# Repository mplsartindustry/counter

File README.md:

# counter

Eurorack module that counts triggers

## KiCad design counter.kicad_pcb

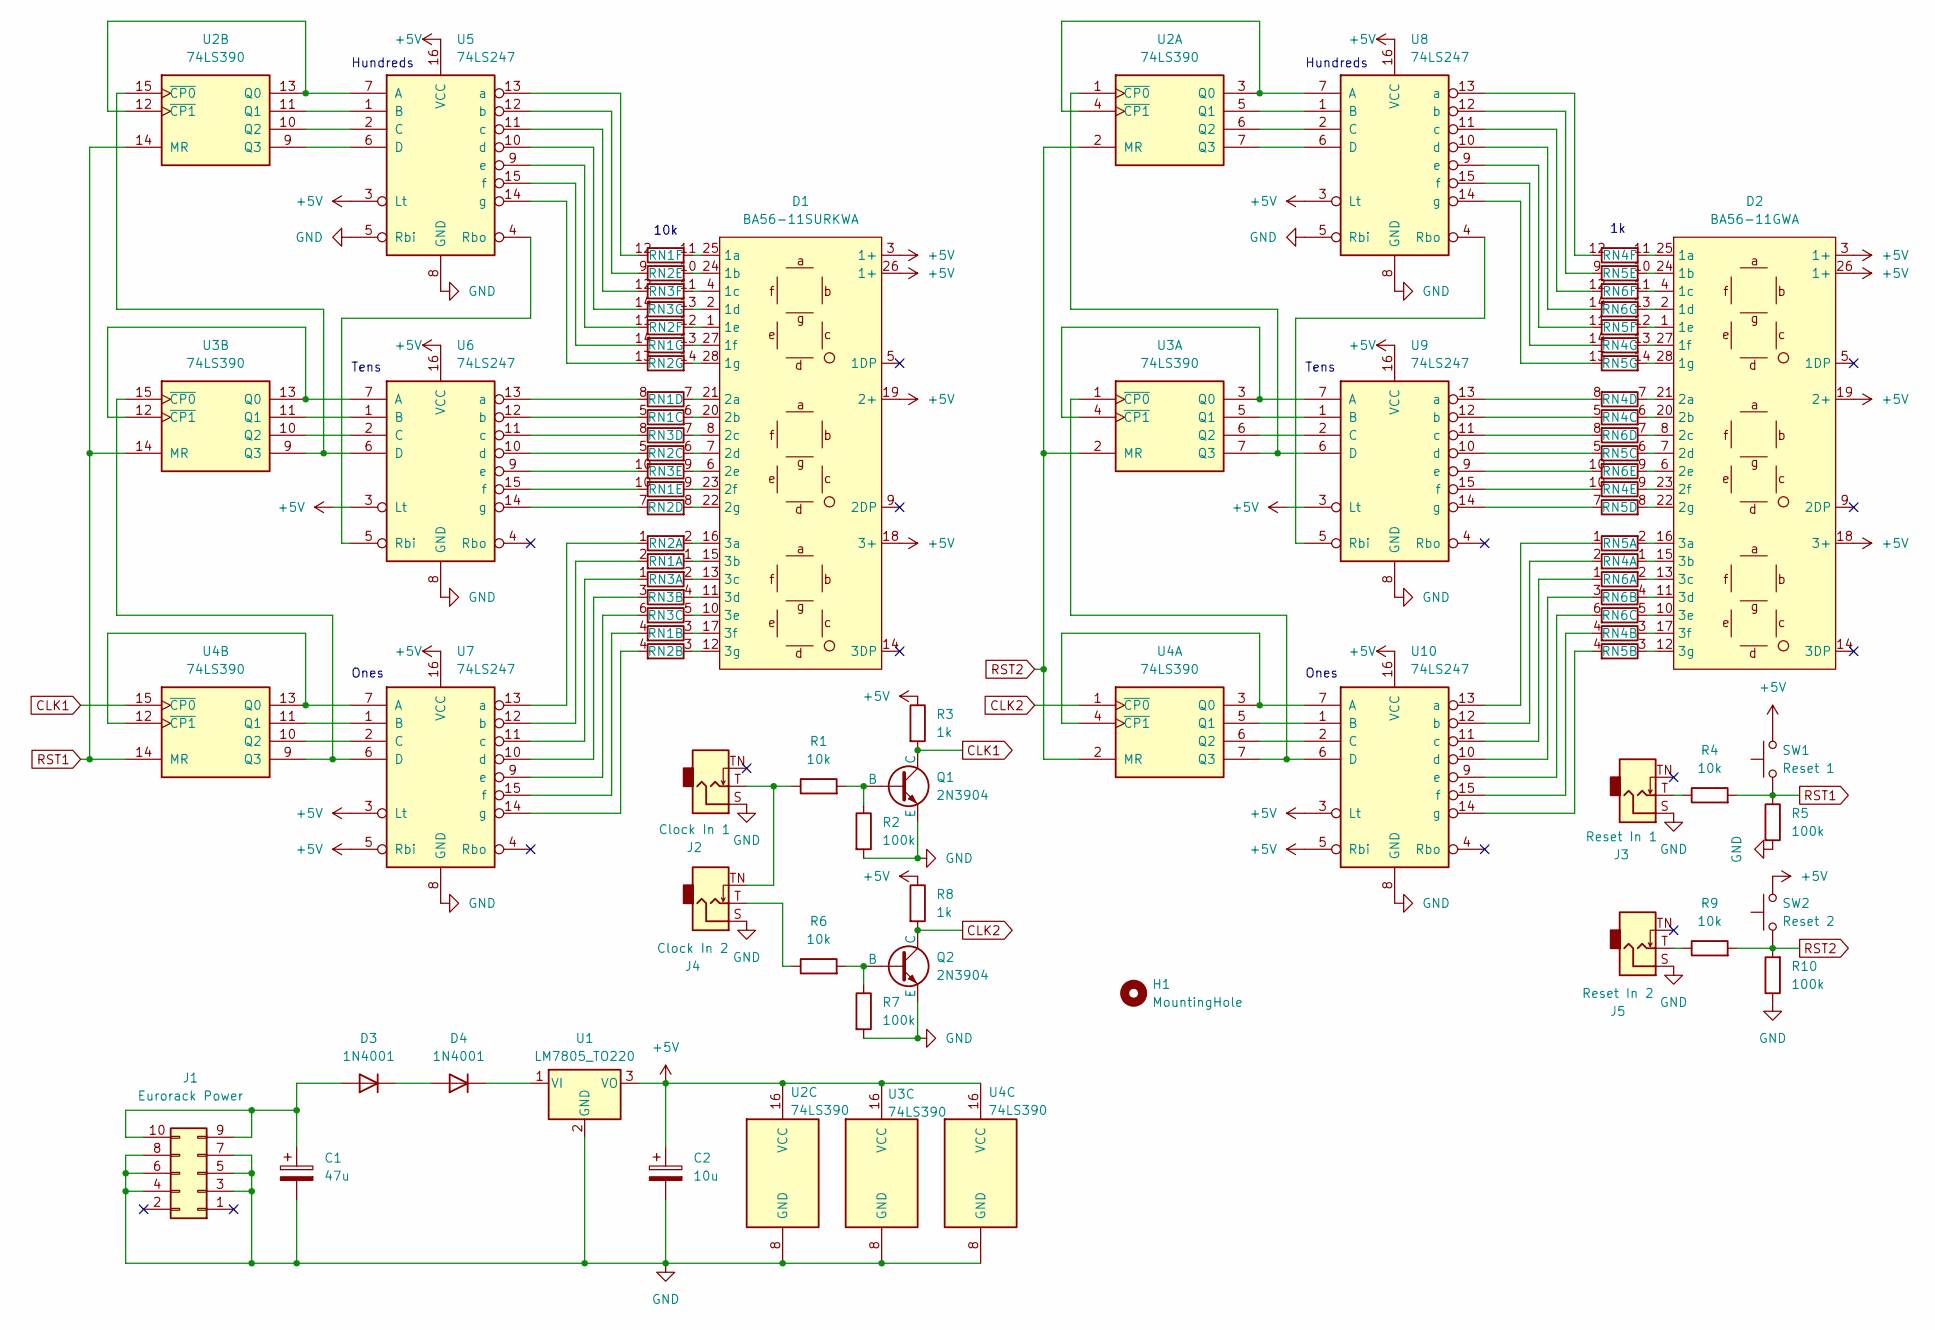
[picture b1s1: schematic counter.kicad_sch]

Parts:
C1: 47u; CP_Radial_D5.0mm_P2.00mm
C2: 10u; CP_Radial_D5.0mm_P2.00mm
D1: BA56-11SURKWA; BA56-11SURKWA_Red_2xSIP
D2: BA56-11GWA; BA56-11GWA_Green_2xSIP
D3, D4: 1N4001; D_DO-41_SOD81_P10.16mm_Horizontal
H1: MountingHole; MountingHole_4.3mm_M4
J1: Eurorack Power; IDC-Header_2x05_P2.54mm_Vertical
J2: Clock In 1; Jack_3.5mm_QingPu_WQP-PJ301BM_Vertical
J3: Reset In 1; Jack_3.5mm_QingPu_WQP-PJ301BM_Vertical
J4: Clock In 2; Jack_3.5mm_QingPu_WQP-PJ301BM_Vertical
J5: Reset In 2; Jack_3.5mm_QingPu_WQP-PJ301BM_Vertical
Q1, Q2: 2N3904; TO-92L_Inline
R1, R4, R6, R9: 10k; R_Axial_DIN0207_L6.3mm_D2.5mm_P7.62mm_Horizontal
R2, R5, R7, R10: 100k; R_Axial_DIN0207_L6.3mm_D2.5mm_P7.62mm_Horizontal
R3, R8: 1k; R_Axial_DIN0207_L6.3mm_D2.5mm_P7.62mm_Horizontal
RN1, RN2, RN3, RN4, RN5, RN6: R_Pack07_SIP_Split; R_Array_SIP14
SW1: Reset 1; SW_CK_D6R40_Red
SW2: Reset 2; SW_CK_D6R50_Green
U1: LM7805_TO220; TO-220-3_Vertical
U2, U3, U4: 74LS390; DIP-16_W7.62mm_Socket_WithChip
U5, U6, U7, U8, U9, U10: 74LS247; DIP-16_W7.62mm_Socket_WithChip

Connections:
+5V: C2.1, D1.3 (1+), D1.18 (3+), D1.19 (2+), D1.26 (1+), D2.3 (1+), D2.18 (3+), D2.19 (2+), D2.26 (1+), R3.1, R8.1, SW1.2, SW2.2, U1.3 (VO), U2.16 (VCC), U3.16 (VCC), U4.16 (VCC), U5.3 (Lt), U5.16 (VCC), U6.3 (Lt), U6.16 (VCC), U7.3 (Lt), U7.5 (Rbi), U7.16 (VCC), U8.3 (Lt), U8.16 (VCC), U9.3 (Lt), U9.16 (VCC), U10.3 (Lt), U10.5 (Rbi), U10.16 (VCC)
CLK1: Q1.1 (C), R3.2, U4.15 (~CP0)
CLK2: Q2.1 (C), R8.2, U4.1 (~CP0)
GND: C1.2, C2.2, J1.3, J1.4, J1.5, J1.6, J1.7, J1.8, J2.S, J3.S, J4.S, J5.S, Q1.3 (E), Q2.3 (E), R2.2, R5.2, R7.2, R10.1, U1.2 (GND), U2.8 (GND), U3.8 (GND), U4.8 (GND), U5.5 (Rbi), U5.8 (GND), U6.8 (GND), U7.8 (GND), U8.5 (Rbi), U8.8 (GND), U9.8 (GND), U10.8 (GND)
unnamed: D1.25 (1a), RN1.11 (R6.1)
unnamed: D1.24 (1b), RN2.10 (R5.2)
unnamed: D1.4 (1c), RN3.11 (R6.1)
unnamed: D1.2 (1d), RN3.13 (R7.1)
unnamed: D1.1 (1e), RN2.12 (R6.2)
unnamed: D1.27 (1f), RN1.13 (R7.1)
unnamed: D1.28 (1g), RN2.14 (R7.2)
unnamed: D1.21 (2a), RN1.7 (R4.1)
unnamed: D1.20 (2b), RN1.6 (R3.2)
unnamed: D1.8 (2c), RN3.7 (R4.1)
unnamed: D1.7 (2d), RN2.6 (R3.2)
unnamed: D1.6 (2e), RN3.9 (R5.1)
unnamed: D1.23 (2f), RN1.9 (R5.1)
unnamed: D1.22 (2g), RN2.8 (R4.2)
unnamed: D1.16 (3a), RN2.2 (R1.2)
unnamed: D1.15 (3b), RN1.1 (R1.1)
unnamed: D1.13 (3c), RN3.2 (R1.2)
unnamed: D1.11 (3d), RN3.4 (R2.2)
unnamed: D1.10 (3e), RN3.5 (R3.1)
unnamed: D1.17 (3f), RN1.3 (R2.1)
unnamed: D1.12 (3g), RN2.3 (R2.1)
unnamed: D2.25 (1a), RN4.11 (R6.1)
unnamed: D2.24 (1b), RN5.10 (R5.2)
unnamed: D2.4 (1c), RN6.11 (R6.1)
unnamed: D2.2 (1d), RN6.13 (R7.1)
unnamed: D2.1 (1e), RN5.12 (R6.2)
unnamed: D2.27 (1f), RN4.13 (R7.1)
unnamed: D2.28 (1g), RN5.14 (R7.2)
unnamed: D2.21 (2a), RN4.7 (R4.1)
unnamed: D2.20 (2b), RN4.6 (R3.2)
unnamed: D2.8 (2c), RN6.7 (R4.1)
unnamed: D2.7 (2d), RN5.6 (R3.2)
unnamed: D2.6 (2e), RN6.9 (R5.1)
unnamed: D2.23 (2f), RN4.9 (R5.1)
unnamed: D2.22 (2g), RN5.8 (R4.2)
unnamed: D2.16 (3a), RN5.2 (R1.2)
unnamed: D2.15 (3b), RN4.1 (R1.1)
unnamed: D2.13 (3c), RN6.2 (R1.2)
unnamed: D2.11 (3d), RN6.4 (R2.2)
unnamed: D2.10 (3e), RN6.5 (R3.1)
unnamed: D2.17 (3f), RN4.3 (R2.1)
unnamed: D2.12 (3g), RN5.3 (R2.1)
unnamed: C1.1, D3.2 (A), J1.9, J1.10
unnamed: D3.1 (K), D4.2 (A)
unnamed: D4.1 (K), U1.1 (VI)
unnamed: J2.T, J4.TN, R1.1
unnamed: J3.T, R4.1
unnamed: J4.T, R6.1
unnamed: J5.T, R9.1
unnamed: Q1.2 (B), R1.2, R2.1
unnamed: Q2.2 (B), R6.2, R7.1
unnamed: RN1.2 (R1.2), U7.12 (b)
unnamed: RN1.4 (R2.2), U7.15 (f)
unnamed: RN1.5 (R3.1), U6.12 (b)
unnamed: RN1.8 (R4.2), U6.13 (a)
unnamed: RN1.10 (R5.2), U6.15 (f)
unnamed: RN1.12 (R6.2), U5.13 (a)
unnamed: RN1.14 (R7.2), U5.15 (f)
unnamed: RN2.1 (R1.1), U7.13 (a)
unnamed: RN2.4 (R2.2), U7.14 (g)
unnamed: RN2.5 (R3.1), U6.10 (d)
unnamed: RN2.7 (R4.1), U6.14 (g)
unnamed: RN2.9 (R5.1), U5.12 (b)
unnamed: RN2.11 (R6.1), U5.9 (e)
unnamed: RN2.13 (R7.1), U5.14 (g)
unnamed: RN3.1 (R1.1), U7.11 (c)
unnamed: RN3.3 (R2.1), U7.10 (d)
unnamed: RN3.6 (R3.2), U7.9 (e)
unnamed: RN3.8 (R4.2), U6.11 (c)
unnamed: RN3.10 (R5.2), U6.9 (e)
unnamed: RN3.12 (R6.2), U5.11 (c)
unnamed: RN3.14 (R7.2), U5.10 (d)
unnamed: RN4.2 (R1.2), U10.12 (b)
unnamed: RN4.4 (R2.2), U10.15 (f)
unnamed: RN4.5 (R3.1), U9.12 (b)
unnamed: RN4.8 (R4.2), U9.13 (a)
unnamed: RN4.10 (R5.2), U9.15 (f)
unnamed: RN4.12 (R6.2), U8.13 (a)
unnamed: RN4.14 (R7.2), U8.15 (f)
unnamed: RN5.1 (R1.1), U10.13 (a)
unnamed: RN5.4 (R2.2), U10.14 (g)
unnamed: RN5.5 (R3.1), U9.10 (d)
unnamed: RN5.7 (R4.1), U9.14 (g)
unnamed: RN5.9 (R5.1), U8.12 (b)
unnamed: RN5.11 (R6.1), U8.9 (e)
unnamed: RN5.13 (R7.1), U8.14 (g)
unnamed: RN6.1 (R1.1), U10.11 (c)
unnamed: RN6.3 (R2.1), U10.10 (d)
unnamed: RN6.6 (R3.2), U10.9 (e)
unnamed: RN6.8 (R4.2), U9.11 (c)
unnamed: RN6.10 (R5.2), U9.9 (e)
unnamed: RN6.12 (R6.2), U8.11 (c)
unnamed: RN6.14 (R7.2), U8.10 (d)
unnamed: U2.3 (Q0), U2.4 (~CP1), U8.7 (A)
unnamed: U2.5 (Q1), U8.1 (B)
unnamed: U2.6 (Q2), U8.2 (C)
unnamed: U2.7 (Q3), U8.6 (D)
unnamed: U2.1 (~CP0), U3.7 (Q3), U9.6 (D)
unnamed: U2.12 (~CP1), U2.13 (Q0), U5.7 (A)
unnamed: U2.11 (Q1), U5.1 (B)
unnamed: U2.10 (Q2), U5.2 (C)
unnamed: U2.9 (Q3), U5.6 (D)
unnamed: U2.15 (~CP0), U3.9 (Q3), U6.6 (D)
unnamed: U3.3 (Q0), U3.4 (~CP1), U9.7 (A)
unnamed: U3.5 (Q1), U9.1 (B)
unnamed: U3.6 (Q2), U9.2 (C)
unnamed: U3.12 (~CP1), U3.13 (Q0), U6.7 (A)
unnamed: U3.11 (Q1), U6.1 (B)
unnamed: U3.10 (Q2), U6.2 (C)
unnamed: U3.15 (~CP0), U4.9 (Q3), U7.6 (D)
unnamed: U4.12 (~CP1), U4.13 (Q0), U7.7 (A)
unnamed: U4.11 (Q1), U7.1 (B)
unnamed: U4.10 (Q2), U7.2 (C)
unnamed: U5.4 (Rbo), U6.5 (Rbi)
unnamed: U8.4 (Rbo), U9.5 (Rbi)
unnamed: U4.3 (Q0), U4.4 (~CP1), U10.7 (A)
unnamed: U4.5 (Q1), U10.1 (B)
unnamed: U4.6 (Q2), U10.2 (C)
unnamed: U3.1 (~CP0), U4.7 (Q3), U10.6 (D)
RST1: R4.2, R5.1, SW1.1, U2.14 (MR), U3.14 (MR), U4.14 (MR)
RST2: R9.2, R10.2, SW2.1, U2.2 (MR), U3.2 (MR), U4.2 (MR)

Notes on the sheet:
Ones
Tens
Hundreds
10k

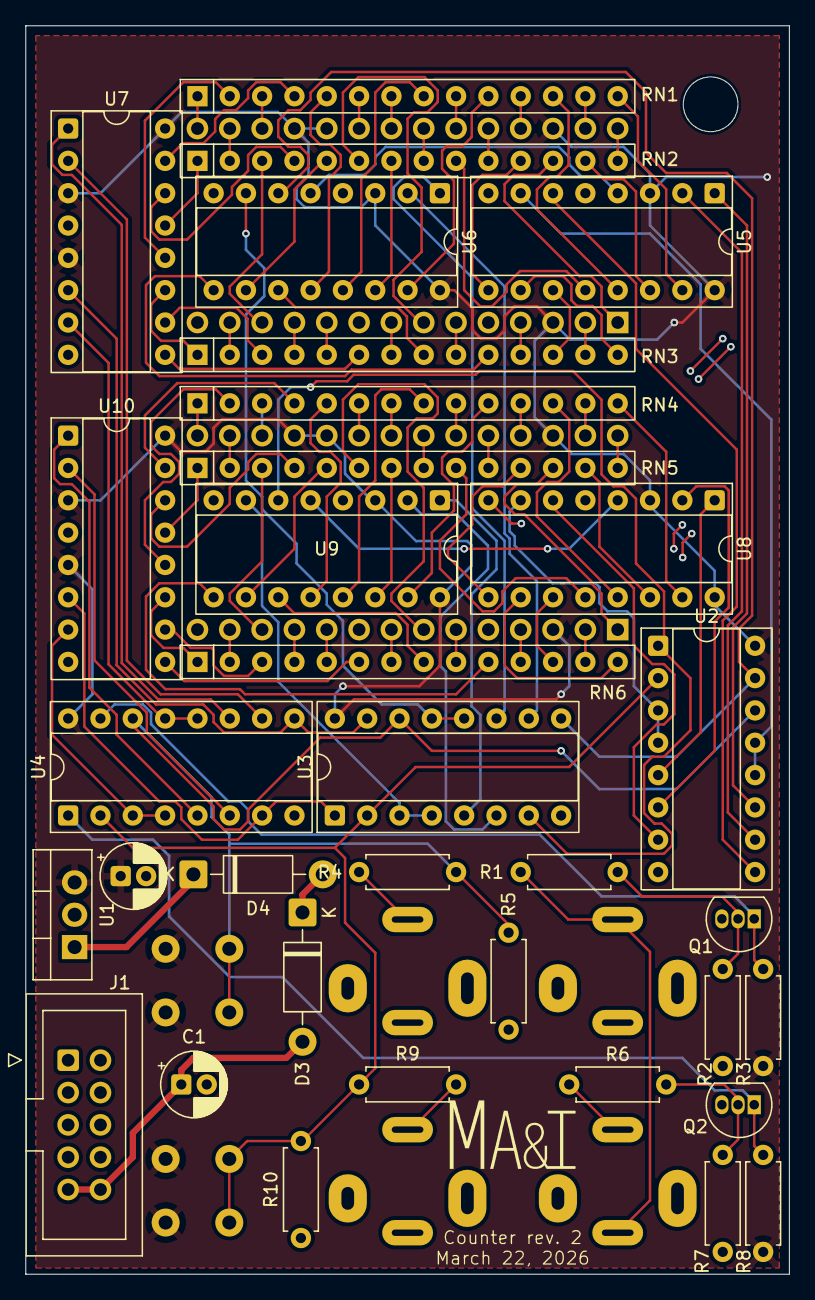
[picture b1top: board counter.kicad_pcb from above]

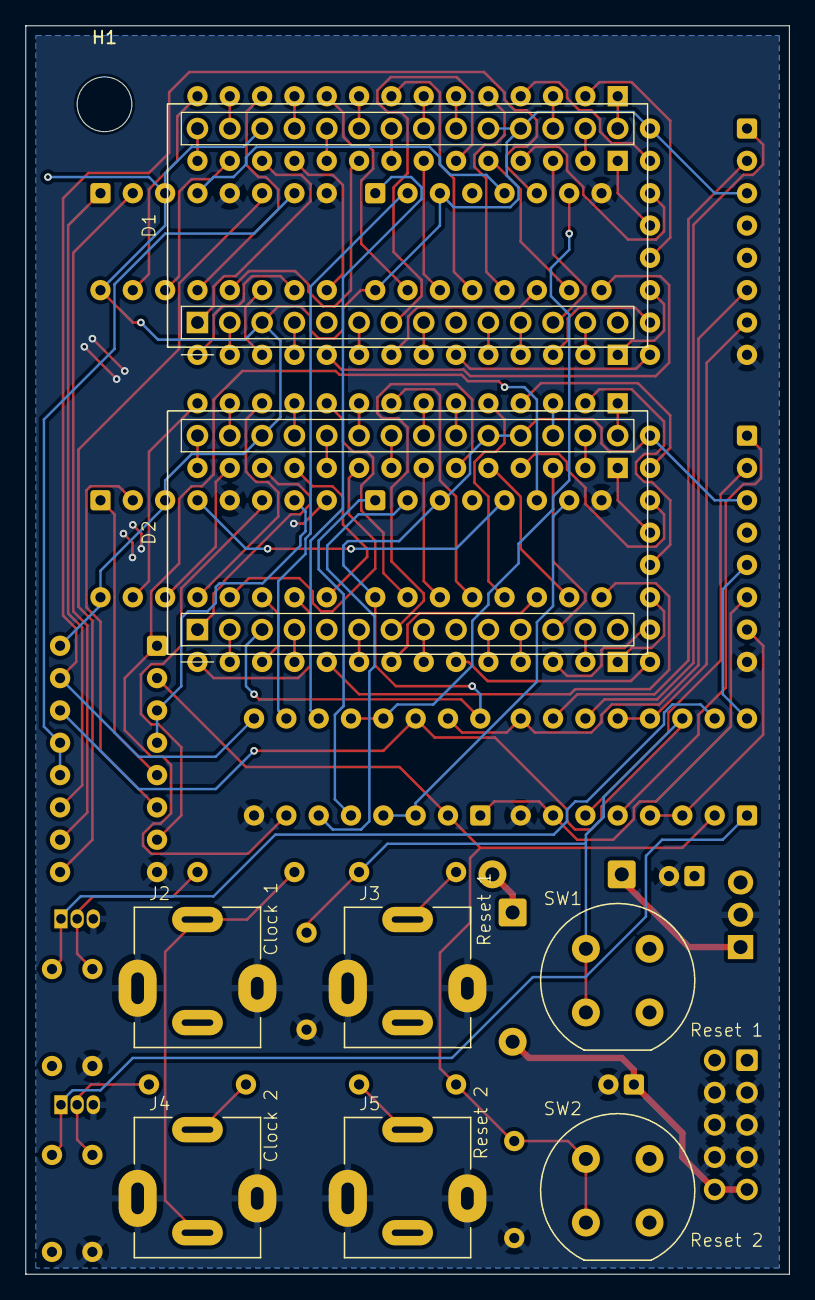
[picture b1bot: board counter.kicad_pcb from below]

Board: 2 copper layers, 60.0 x 98.1 mm, 42 parts (9 on the bottom side), 125 nets.

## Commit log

2025-09-28 Add panel
2025-10-04 Fix ones place digit being backwards
2025-11-14 Add diodes to reduce regulator input voltage
2026-01-02 Export gerbers
2026-03-22 Rev. 2
2026-03-25 Add pad for standoff to panel
